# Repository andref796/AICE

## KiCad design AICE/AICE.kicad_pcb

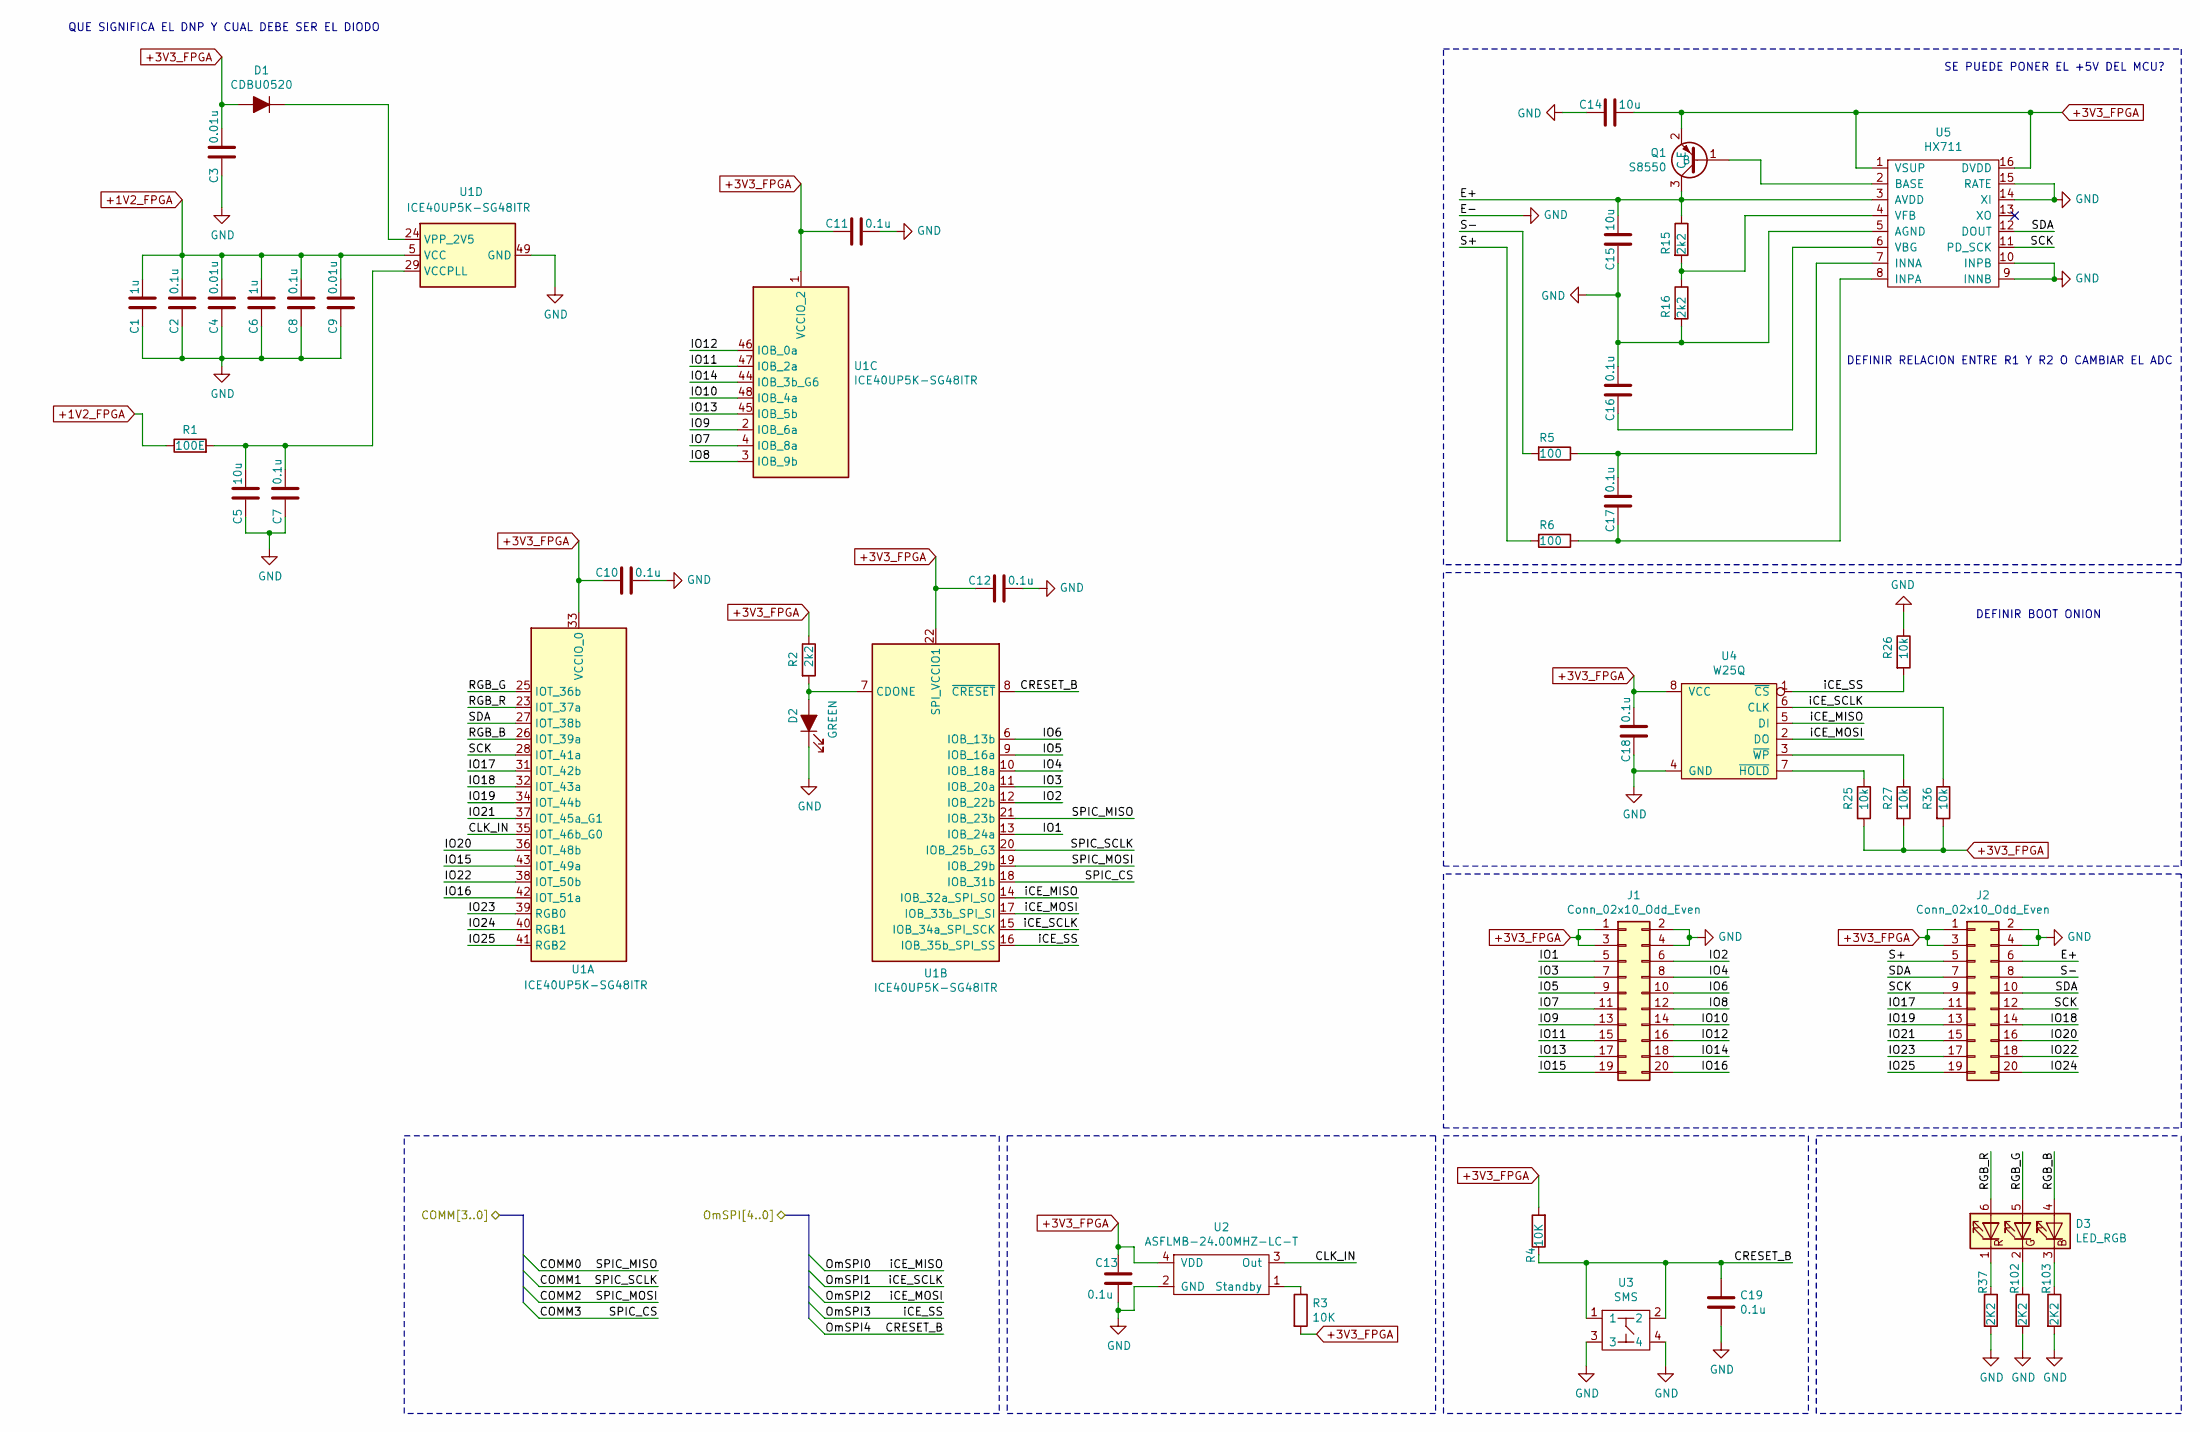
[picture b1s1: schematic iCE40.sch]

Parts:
C1, C6: 1u; C_0603_1608Metric
C2, C7, C8, C10, C11, C12, C13, C16, C17, C18, C19: 0.1u; C_0603_1608Metric
C3, C4, C9: 0.01u; C_0603_1608Metric
C5, C14, C15: 10u; C_0603_1608Metric
D1: CDBU0520; LED_0603_1608Metric
D2: GREEN; LED_0603_1608Metric
D3: LED_RGB; LED_RGB_Cree-PLCC-6_6x5mm_P2.1mm
J1, J2: Conn_02x10_Odd_Even; PinHeader_2x10_P2.54mm_Vertical
Q1: S8550; SOT-23
R1: 100E; R_0603_1608Metric
R2, R15, R16: 2k2; R_0603_1608Metric
R3, R4: 10K; R_0603_1608Metric
R5, R6: 100; R_0603_1608Metric
R25, R26, R27, R36: 10k; R_0603_1608Metric
R37, R102, R103: 2K2; R_0603_1608Metric
U1: ICE40UP5K-SG48ITR; QFN-48-1EP_7x7mm_P0.5mm_EP5.6x5.6mm
U2: ASFLMB-24.00MHZ-LC-T; ASFLMB
U3: SMS; SMS_BUTTON
U4: W25Q; SOIC-8_5.23x5.23mm_P1.27mm
U5: HX711; SOP-16_4.4x10.4mm_P1.27mm

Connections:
+1V2_FPGA: C1.1, C2.1, C4.1, C6.1, C8.1, C9.1, R1.1, U1.5 (VCC), U1.30 (VCC); also elsewhere on the board
+3V3_FPGA: C3.1, C10.2, C11.2, C12.2, C13.1, C14.1, C18.1, D1.2 (A), J1.1, J1.3, J2.1, J2.3, Q1.2 (E), R2.1, R3.2, R4.2, R25.2, R27.2, R36.2, U1.1 (VCCIO_2), U1.22 (SPI_VCCIO1), U1.33 (VCCIO_0), U2.4 (VDD), U4.8 (VCC), U5.1 (VSUP), U5.16 (DVDD); also elsewhere on the board
/iCE40/CLK_IN: U1.35 (IOT_46b_G0), U2.3 (Out)
/iCE40/COMM0: U1.21 (IOB_23b); also elsewhere on the board
/iCE40/COMM1: U1.20 (IOB_25b_G3); also elsewhere on the board
/iCE40/COMM2: U1.19 (IOB_29b); also elsewhere on the board
/iCE40/COMM3: U1.18 (IOB_31b); also elsewhere on the board
/iCE40/CRESET_B: C19.1, R4.1, U1.8 (~CRESET), U3.1, U3.2; also elsewhere on the board
/iCE40/E+: C15.1, J2.6, Q1.3 (C), R15.1, U5.3 (AVDD)
/iCE40/IO1: J1.5, U1.13 (IOB_24a)
/iCE40/IO2: J1.6, U1.12 (IOB_22b)
/iCE40/IO3: J1.7, U1.11 (IOB_20a)
/iCE40/IO4: J1.8, U1.10 (IOB_18a)
/iCE40/IO5: J1.9, U1.9 (IOB_16a)
/iCE40/IO6: J1.10, U1.6 (IOB_13b)
/iCE40/IO7: J1.11, U1.4 (IOB_8a)
/iCE40/IO8: J1.12, U1.3 (IOB_9b)
/iCE40/IO9: J1.13, U1.2 (IOB_6a)
/iCE40/IO10: J1.14, U1.48 (IOB_4a)
/iCE40/IO11: J1.15, U1.47 (IOB_2a)
/iCE40/IO12: J1.16, U1.46 (IOB_0a)
/iCE40/IO13: J1.17, U1.45 (IOB_5b)
/iCE40/IO14: J1.18, U1.44 (IOB_3b_G6)
/iCE40/IO15: J1.19, U1.43 (IOT_49a)
/iCE40/IO16: J1.20, U1.42 (IOT_51a)
/iCE40/IO17: J2.11, U1.31 (IOT_42b)
/iCE40/IO18: J2.14, U1.32 (IOT_43a)
/iCE40/IO19: J2.13, U1.34 (IOT_44b)
/iCE40/IO20: J2.16, U1.36 (IOT_48b)
/iCE40/IO21: J2.15, U1.37 (IOT_45a_G1)
/iCE40/IO22: J2.18, U1.38 (IOT_50b)
/iCE40/IO23: J2.17, U1.39 (RGB0)
/iCE40/IO24: J2.20, U1.40 (RGB1)
/iCE40/IO25: J2.19, U1.41 (RGB2)
/iCE40/OmSPI0: U1.14 (IOB_32a_SPI_SO), U4.5 (DI); also elsewhere on the board
/iCE40/OmSPI1: R36.1, U1.15 (IOB_34a_SPI_SCK), U4.6 (CLK); also elsewhere on the board
/iCE40/OmSPI2: U1.17 (IOB_33b_SPI_SI), U4.2 (DO); also elsewhere on the board
/iCE40/OmSPI3: R26.2, U1.16 (IOB_35b_SPI_SS), U4.1 (~CS~); also elsewhere on the board
/iCE40/RGB_B: D3.4 (BA), U1.26 (IOT_39a)
/iCE40/RGB_G: D3.5 (GA), U1.25 (IOT_36b)
/iCE40/RGB_R: D3.6 (RA), U1.23 (IOT_37a)
/iCE40/S+: J2.5, R6.2
/iCE40/S-: J2.8, R5.2
GND: C1.2, C2.2, C3.2, C4.2, C5.2, C6.2, C7.2, C8.2, C9.2, C10.1, C11.1, C12.1, C13.2, C14.2, C15.2, C16.1, C18.2, C19.2, D2.1 (K), J1.2, J1.4, J2.2, J2.4, R16.2, R26.1, R37.2, R102.2, R103.2, U1.49 (GND), U2.2 (GND), U3.3, U3.4, U4.4 (GND), U5.5 (AGND), U5.9 (INNB), U5.10 (INPB), U5.14 (XI), U5.15 (RATE); also elsewhere on the board
unnamed: C5.1, C7.1, R1.2, U1.29 (VCCPLL)
unnamed: C16.2, U5.6 (VBG)
unnamed: C17.1, R5.1, U5.7 (INNA)
unnamed: C17.2, R6.1, U5.8 (INPA)
unnamed: D1.1 (K), U1.24 (VPP_2V5)
unnamed: D2.2 (A), R2.2, U1.7 (CDONE)
unnamed: D3.1 (RK), R37.1
unnamed: D3.2 (GK), R102.1
unnamed: D3.3 (BK), R103.1
unnamed: Q1.1 (B), U5.2 (BASE)
unnamed: R3.1, U2.1 (Standby)
unnamed: R15.2, R16.1, U5.4 (VFB)
unnamed: R25.1, U4.7 (~HOLD)
unnamed: R27.1, U4.3 (~WP)

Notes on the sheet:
SE PUEDE PONER EL +5V DEL MCU?
QUE SIGNIFICA EL DNP Y CUAL DEBE SER EL DIODO
DEFINIR BOOT ONION
DEFINIR RELACION ENTRE R1 Y R2 O CAMBIAR EL ADC

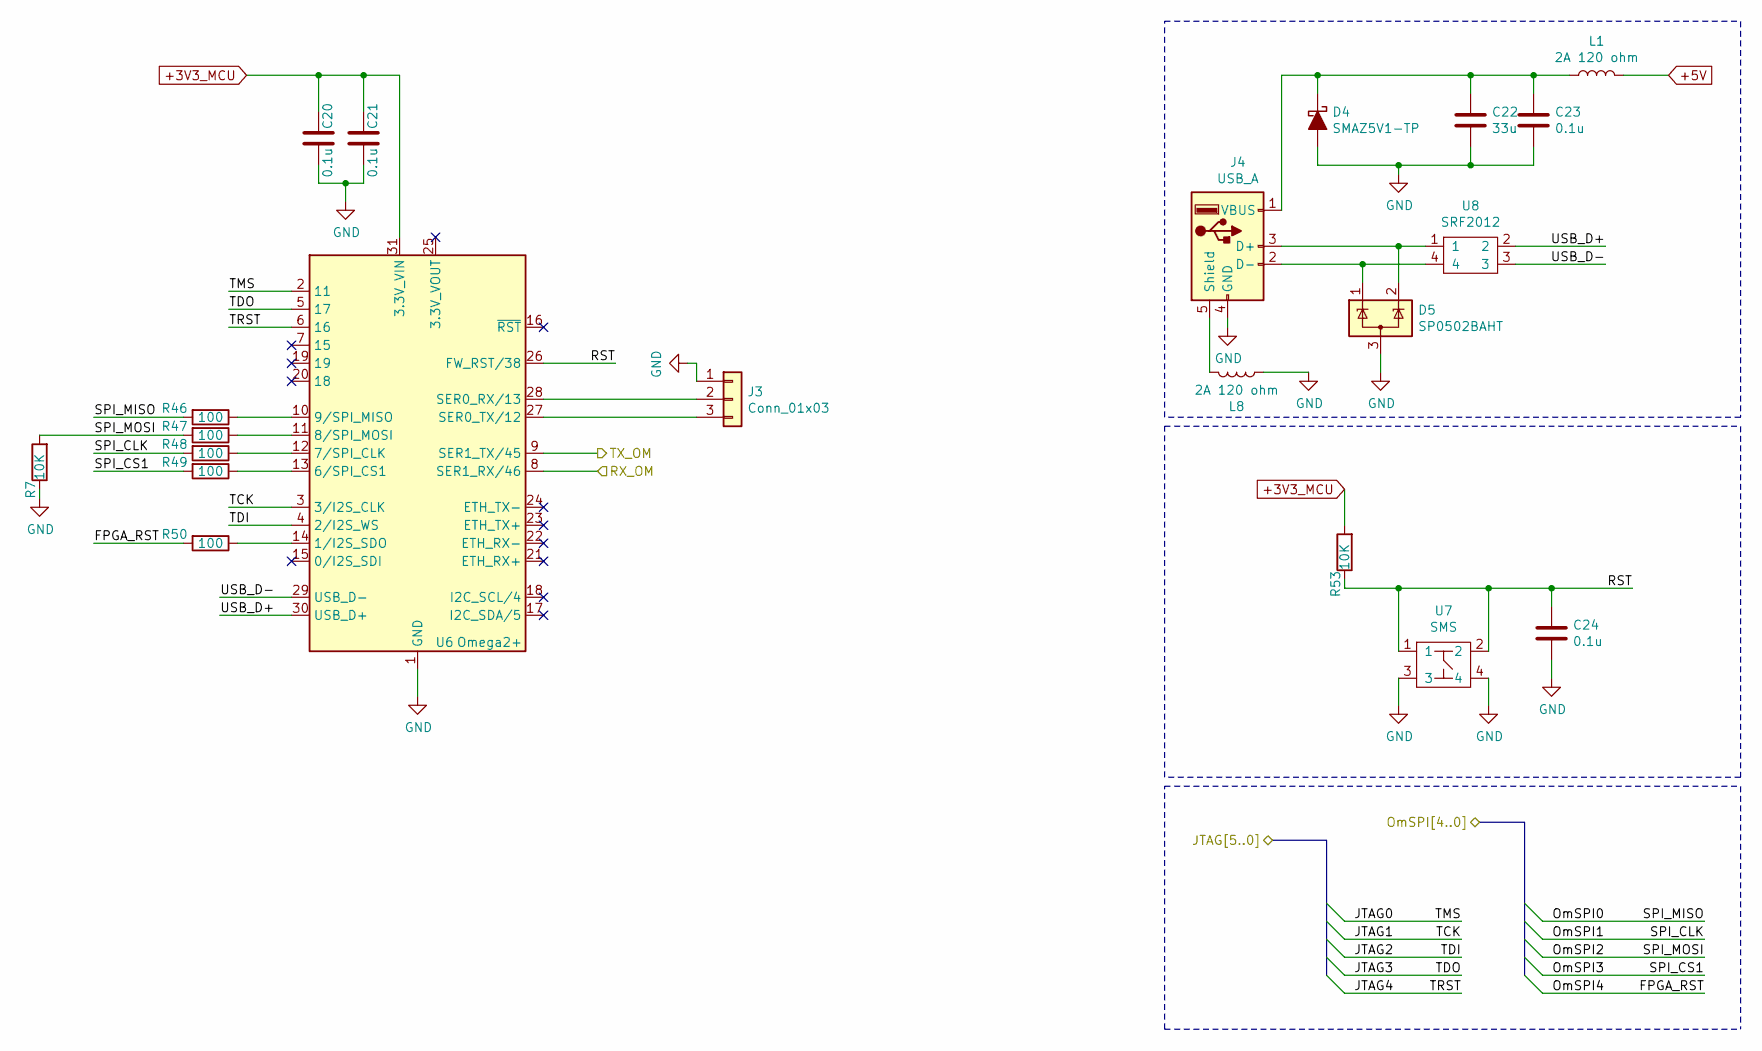
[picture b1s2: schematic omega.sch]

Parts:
C20, C21, C23, C24: 0.1u; C_0603_1608Metric
C22: 33u; CP_Radial_D5.0mm_P2.00mm
D4: SMAZ5V1-TP; D_SMA
D5: SP0502BAHT; SOT-23
J3: Conn_01x03; PinHeader_1x03_P2.54mm_Vertical
J4: USB_A; USB_A_Stewart_SS-52100-001_Horizontal
L1, L8: 2A 120 ohm; L_0805_2012Metric
R7, R53: 10K; R_0603_1608Metric
R46, R47, R48, R49, R50: 100; R_0603_1608Metric
U6: Omega2+; Onion_Omega2+
U7: SMS; SMS_BUTTON
U8: SRF2012

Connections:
+3V3_MCU: C20.2, C21.2, R53.2, U6.31 (3.3V_VIN); also elsewhere on the board
+5V: L1.2; also elsewhere on the board
/iCE40/CRESET_B: R50.2; also elsewhere on the board
/iCE40/OmSPI0: R46.2; also elsewhere on the board
/iCE40/OmSPI1: R48.2; also elsewhere on the board
/iCE40/OmSPI2: R7.2, R47.2; also elsewhere on the board
/iCE40/OmSPI3: R49.2; also elsewhere on the board
/omega/JTAG0: U6.2 (11); also elsewhere on the board
/omega/JTAG1: U6.3 (3/I2S_CLK); also elsewhere on the board
/omega/JTAG2: U6.4 (2/I2S_WS); also elsewhere on the board
/omega/JTAG3: U6.5 (17); also elsewhere on the board
/omega/JTAG4: U6.6 (16); also elsewhere on the board
/omega/RST: C24.1, R53.1, U6.26 (FW_RST/38), U7.1, U7.2
/omega/RX_OM: U6.8 (SER1_RX/46); also elsewhere on the board
/omega/USB_D+: U6.30 (USB_D+), U8.2
/omega/USB_D-: U6.29 (USB_D-), U8.3
/sipeedm1w/RX_M1: U6.9 (SER1_TX/45); also elsewhere on the board
GND: C20.1, C21.1, C22.2, C23.2, C24.2, D4.2 (A), D5.3 (A), J3.1, J4.4 (GND), L8.1, R7.1, U6.1 (GND), U6.32 (GND), U7.3, U7.4; also elsewhere on the board
unnamed: C22.1, C23.1, D4.1 (K), J4.1 (VBUS), L1.1
unnamed: D5.1 (K), J4.2 (D-), U8.4
unnamed: D5.2 (K), J4.3 (D+), U8.1
unnamed: J3.2, U6.28 (SER0_RX/13)
unnamed: J3.3, U6.27 (SER0_TX/12)
unnamed: J4.5 (Shield), L8.2
unnamed: R46.1, U6.10 (9/SPI_MISO)
unnamed: R47.1, U6.11 (8/SPI_MOSI)
unnamed: R48.1, U6.12 (7/SPI_CLK)
unnamed: R49.1, U6.13 (6/SPI_CS1)
unnamed: R50.1, U6.14 (1/I2S_SDO)

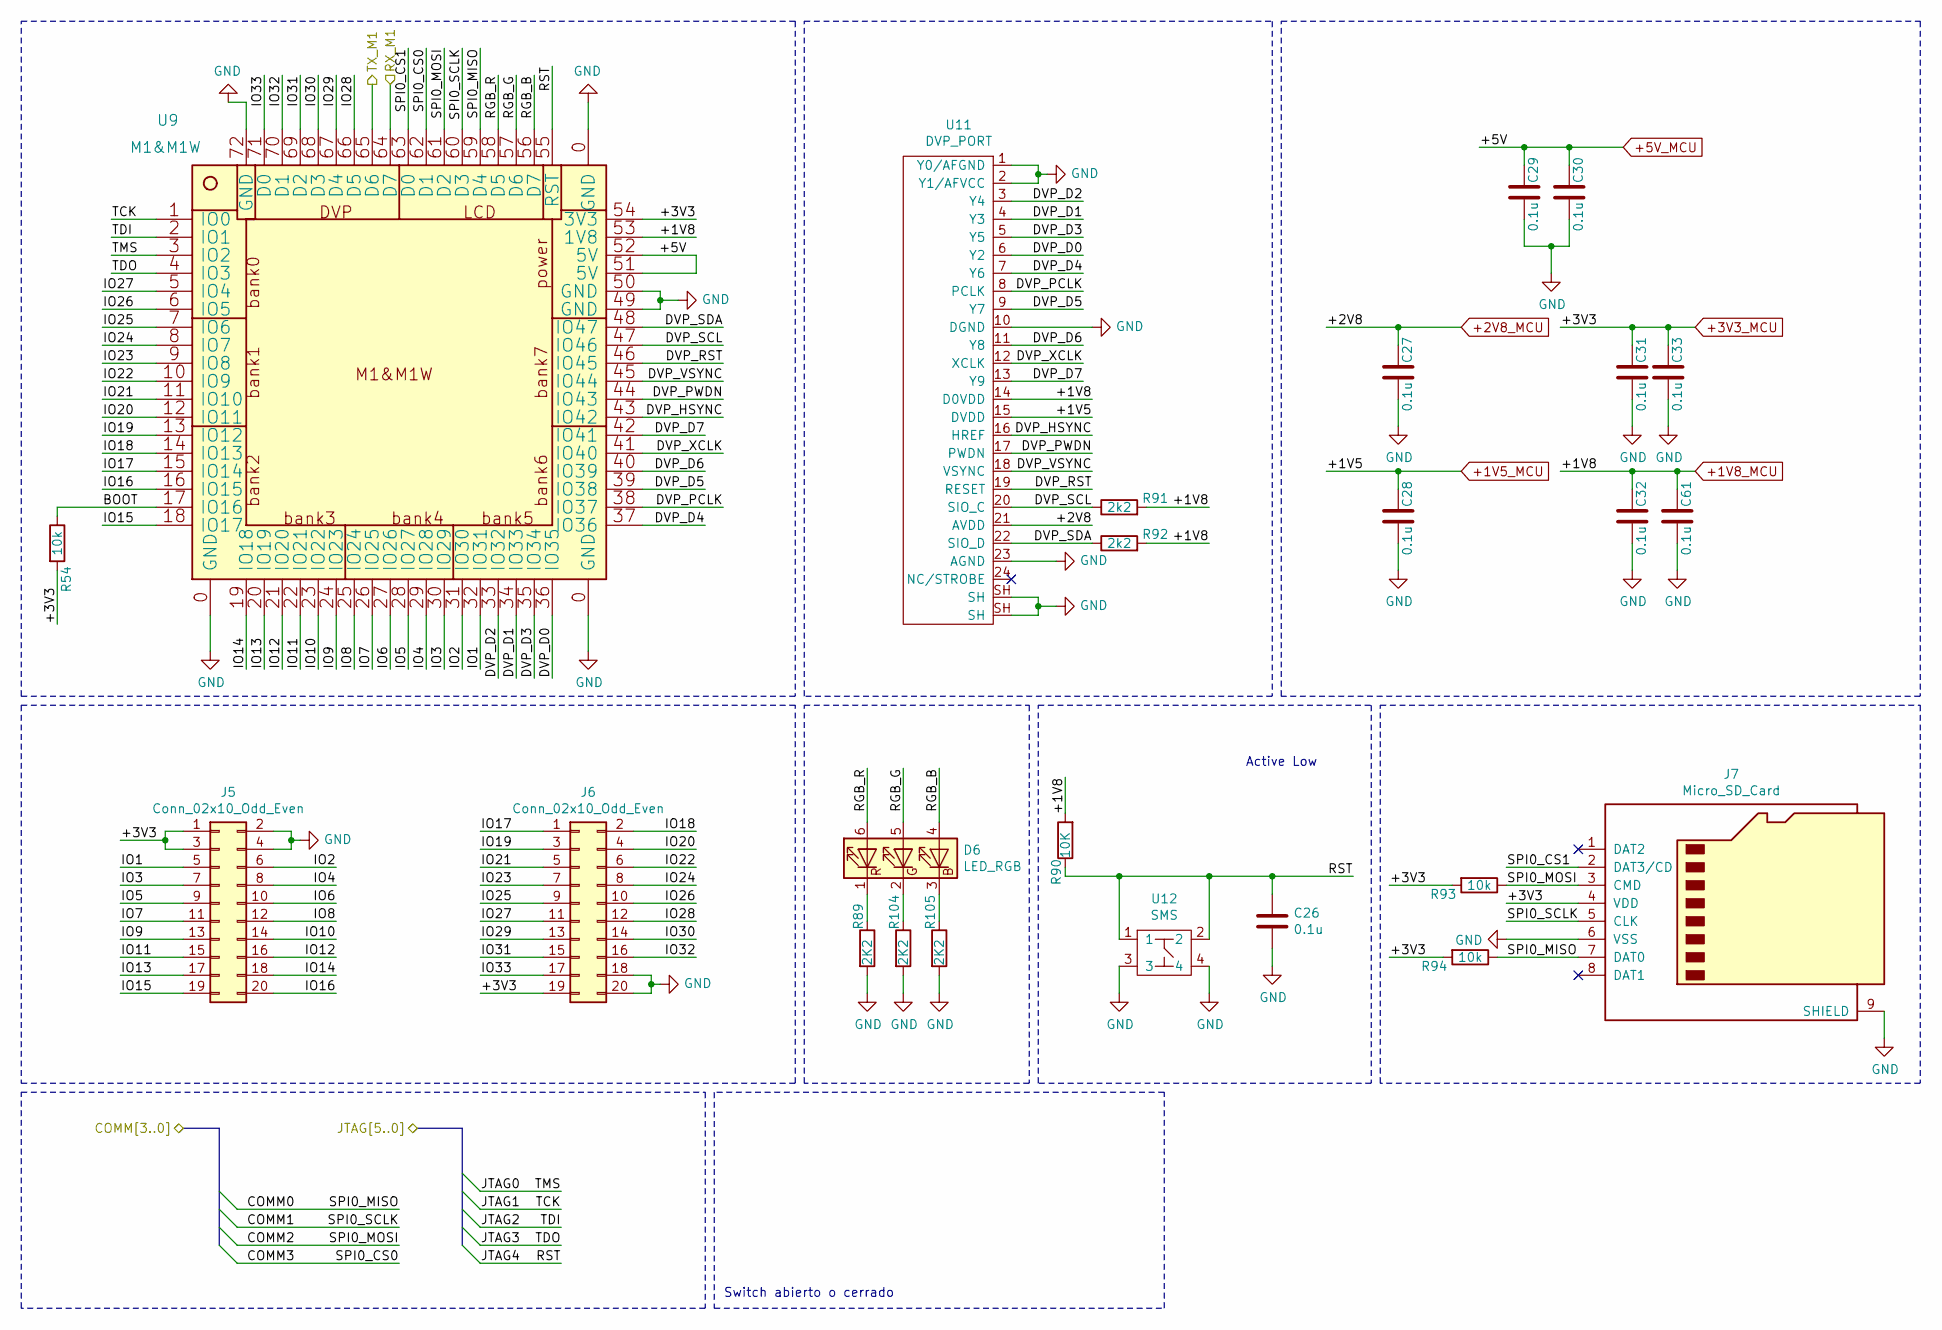
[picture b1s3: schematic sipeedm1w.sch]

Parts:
C26, C27, C28, C29, C30, C31, C32, C33, C61: 0.1u; C_0603_1608Metric
D6: LED_RGB; LED_RGB_Cree-PLCC-6_6x5mm_P2.1mm
J5, J6: Conn_02x10_Odd_Even; PinHeader_2x10_P2.54mm_Vertical
J7: Micro_SD_Card; microSD_HC_Wuerth_693072010801
R54, R93, R94: 10k; R_0603_1608Metric
R89, R104, R105: 2K2; R_0603_1608Metric
R90: 10K; R_0603_1608Metric
R91, R92: 2k2; R_0603_1608Metric
U9: M1&M1W; QFN-72_25.4x25.4_Pitch1.27mm
U11: DVP_PORT; Molex_502231-2400_1x24-1SH_P0.5mm_Vertical
U12: SMS; SMS_BUTTON

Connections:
+1V5_MCU: C28.2, U11.15 (DVDD); also elsewhere on the board
+1V8_MCU: C32.2, C61.2, R90.2, R91.2, R92.2, U9.53 (1V8), U11.14 (D0VDD); also elsewhere on the board
+2V8_MCU: C27.2, U11.21 (AVDD); also elsewhere on the board
+3V3_MCU: C31.2, C33.2, J5.1, J5.3, J6.19, J7.4 (VDD), R54.2, R93.2, R94.2, U9.54 (3V3); also elsewhere on the board
+5V: C29.2, C30.2, U9.51 (5V), U9.52 (5V); also elsewhere on the board
/iCE40/COMM0: J7.7 (DAT0), R94.1, U9.59 (D4); also elsewhere on the board
/iCE40/COMM1: J7.5 (CLK), U9.60 (D3); also elsewhere on the board
/iCE40/COMM2: J7.3 (CMD), R93.1, U9.61 (D2); also elsewhere on the board
/iCE40/COMM3: U9.62 (D1); also elsewhere on the board
/omega/JTAG0: U9.3 (IO2); also elsewhere on the board
/omega/JTAG1: U9.1 (IO0); also elsewhere on the board
/omega/JTAG2: U9.2 (IO1); also elsewhere on the board
/omega/JTAG3: U9.4 (IO3); also elsewhere on the board
/omega/JTAG4: C26.1, R90.1, U9.55 (RST), U12.1, U12.2; also elsewhere on the board
/omega/RX_OM: U9.65 (D6); also elsewhere on the board
/sipeedm1w/BOOT: R54.1, U9.17 (IO16)
/sipeedm1w/DVP_D0: U9.36 (IO35), U11.6 (Y2)
/sipeedm1w/DVP_D1: U9.34 (IO33), U11.4 (Y3)
/sipeedm1w/DVP_D2: U9.33 (IO32), U11.3 (Y4)
/sipeedm1w/DVP_D3: U9.35 (IO34), U11.5 (Y5)
/sipeedm1w/DVP_D4: U9.37 (IO36), U11.7 (Y6)
/sipeedm1w/DVP_D5: U9.39 (IO38), U11.9 (Y7)
/sipeedm1w/DVP_D6: U9.40 (IO39), U11.11 (Y8)
/sipeedm1w/DVP_D7: U9.42 (IO41), U11.13 (Y9)
/sipeedm1w/DVP_HSYNC: U9.43 (IO42), U11.16 (HREF)
/sipeedm1w/DVP_PCLK: U9.38 (IO37), U11.8 (PCLK)
/sipeedm1w/DVP_PWDN: U9.44 (IO43), U11.17 (PWDN)
/sipeedm1w/DVP_RST: U9.46 (IO45), U11.19 (RESET)
/sipeedm1w/DVP_SCL: R91.1, U9.47 (IO46), U11.20 (SIO_C)
/sipeedm1w/DVP_SDA: R92.1, U9.48 (IO47), U11.22 (SIO_D)
/sipeedm1w/DVP_VSYNC: U9.45 (IO44), U11.18 (VSYNC)
/sipeedm1w/DVP_XCLK: U9.41 (IO40), U11.12 (XCLK)
/sipeedm1w/IO1: J5.5, U9.32 (IO31)
/sipeedm1w/IO2: J5.6, U9.31 (IO30)
/sipeedm1w/IO3: J5.7, U9.30 (IO29)
/sipeedm1w/IO4: J5.8, U9.29 (IO28)
/sipeedm1w/IO5: J5.9, U9.28 (IO27)
/sipeedm1w/IO6: J5.10, U9.27 (IO26)
/sipeedm1w/IO7: J5.11, U9.26 (IO25)
/sipeedm1w/IO8: J5.12, U9.25 (IO24)
/sipeedm1w/IO9: J5.13, U9.24 (IO23)
/sipeedm1w/IO10: J5.14, U9.23 (IO22)
/sipeedm1w/IO11: J5.15, U9.22 (IO21)
/sipeedm1w/IO12: J5.16, U9.21 (IO20)
/sipeedm1w/IO13: J5.17, U9.20 (IO19)
/sipeedm1w/IO14: J5.18, U9.19 (IO18)
/sipeedm1w/IO15: J5.19, U9.18 (IO17)
/sipeedm1w/IO16: J5.20, U9.16 (IO15)
/sipeedm1w/IO17: J6.1, U9.15 (IO14)
/sipeedm1w/IO18: J6.2, U9.14 (IO13)
/sipeedm1w/IO19: J6.3, U9.13 (IO12)
/sipeedm1w/IO20: J6.4, U9.12 (IO11)
/sipeedm1w/IO21: J6.5, U9.11 (IO10)
/sipeedm1w/IO22: J6.6, U9.10 (IO9)
/sipeedm1w/IO23: J6.7, U9.9 (IO8)
/sipeedm1w/IO24: J6.8, U9.8 (IO7)
/sipeedm1w/IO25: J6.9, U9.7 (IO6)
/sipeedm1w/IO26: J6.10, U9.6 (IO5)
/sipeedm1w/IO27: J6.11, U9.5 (IO4)
/sipeedm1w/IO28: J6.12, U9.66 (D5)
/sipeedm1w/IO29: J6.13, U9.67 (D4)
/sipeedm1w/IO30: J6.14, U9.68 (D3)
/sipeedm1w/IO31: J6.15, U9.69 (D2)
/sipeedm1w/IO32: J6.16, U9.70 (D1)
/sipeedm1w/IO33: J6.17, U9.71 (D0)
/sipeedm1w/RGB_B: D6.4 (BA), U9.56 (D7)
/sipeedm1w/RGB_G: D6.5 (GA), U9.57 (D6)
/sipeedm1w/RGB_R: D6.6 (RA), U9.58 (D5)
/sipeedm1w/RX_M1: U9.64 (D7); also elsewhere on the board
/sipeedm1w/SPI0_CS1: J7.2 (DAT3/CD), U9.63 (D0)
GND: C26.2, C27.1, C28.1, C29.1, C30.1, C31.1, C32.1, C33.1, C61.1, J5.2, J5.4, J6.18, J6.20, J7.6 (VSS), J7.9 (SHIELD), R89.2, R104.2, R105.2, U9.0 (GND), U9.49 (GND), U9.50 (GND), U9.72 (GND), U11.1 (Y0/AFGND), U11.2 (Y1/AFVCC), U11.10 (DGND), U11.23 (AGND), U11.SH, U12.3, U12.4; also elsewhere on the board
unnamed: D6.1 (RK), R89.1
unnamed: D6.2 (GK), R104.1
unnamed: D6.3 (BK), R105.1

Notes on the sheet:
Switch abierto o cerrado
Active Low

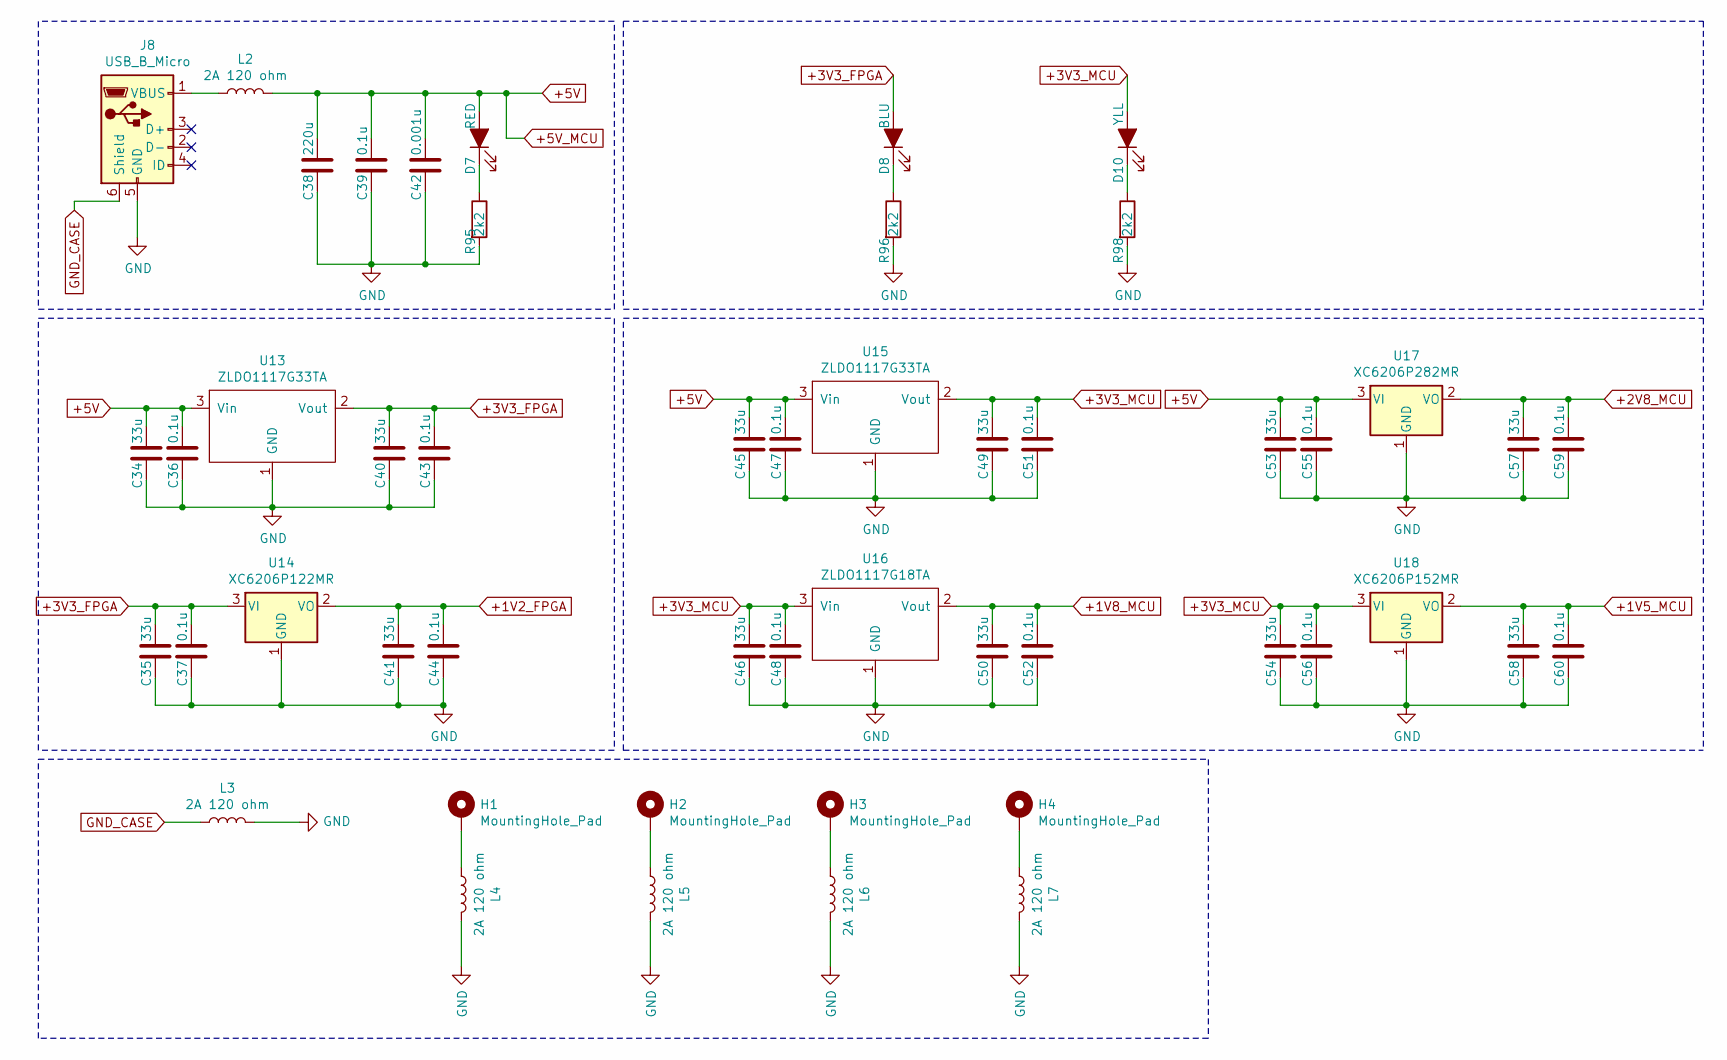
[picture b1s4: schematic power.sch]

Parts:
C34, C35, C40, C41, C45, C46, C49, C50, C53, C54, C57, C58: 33u; C_0805_2012Metric
C36, C37, C39, C43, C44, C47, C48, C51, C52, C55, C56, C59, C60: 0.1u; C_0603_1608Metric
C38: 220u; C_1206_3216Metric
C42: 0.001u; C_0603_1608Metric
D7: RED; LED_0603_1608Metric
D8: BLU; LED_0603_1608Metric
D10: YLL; LED_0603_1608Metric
H1, H2, H3, H4: MountingHole_Pad; MountingHole_2.5mm_Pad
J8: USB_B_Micro; USB_Micro-B_Molex_47346-0001
L2, L3, L4, L5, L6, L7: 2A 120 ohm; L_0805_2012Metric
R95, R96, R98: 2k2; R_0603_1608Metric
U13, U15: ZLDO1117G33TA; SOT-223
U14: XC6206P122MR; SOT-23
U16: ZLDO1117G18TA; SOT-223
U17: XC6206P282MR; SOT-23
U18: XC6206P152MR; SOT-23

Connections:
+1V2_FPGA: C41.1, C44.1, U14.2 (VO); also elsewhere on the board
+1V5_MCU: C58.1, C60.1, U18.2 (VO); also elsewhere on the board
+1V8_MCU: C50.1, C52.1, U16.2 (Vout); also elsewhere on the board
+2V8_MCU: C57.1, C59.1, U17.2 (VO); also elsewhere on the board
+3V3_FPGA: C35.1, C37.1, C40.1, C43.1, D8.2 (A), U13.2 (Vout), U14.3 (VI); also elsewhere on the board
+3V3_MCU: C46.1, C48.1, C49.1, C51.1, C54.1, C56.1, D10.2 (A), U15.2 (Vout), U16.3 (Vin), U18.3 (VI); also elsewhere on the board
+5V: C34.1, C36.1, C38.1, C39.1, C42.1, C45.1, C47.1, C53.1, C55.1, D7.2 (A), L2.2, U13.3 (Vin), U15.3 (Vin), U17.3 (VI); also elsewhere on the board
GND: C34.2, C35.2, C36.2, C37.2, C38.2, C39.2, C40.2, C41.2, C42.2, C43.2, C44.2, C45.2, C46.2, C47.2, C48.2, C49.2, C50.2, C51.2, C52.2, C53.2, C54.2, C55.2, C56.2, C57.2, C58.2, C59.2, C60.2, J8.5 (GND), L3.2, L4.2, L5.2, L6.2, L7.2, R95.2, R96.2, R98.2, U13.1 (GND), U14.1 (GND), U15.1 (GND), U16.1 (GND), U17.1 (GND), U18.1 (GND); also elsewhere on the board
GND_CASE: J8.6 (Shield), L3.1
unnamed: D7.1 (K), R95.1
unnamed: D8.1 (K), R96.1
unnamed: D10.1 (K), R98.1
unnamed: H1.1, L4.1
unnamed: H2.1, L5.1
unnamed: H3.1, L6.1
unnamed: H4.1, L7.1
unnamed: J8.1 (VBUS), L2.1

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
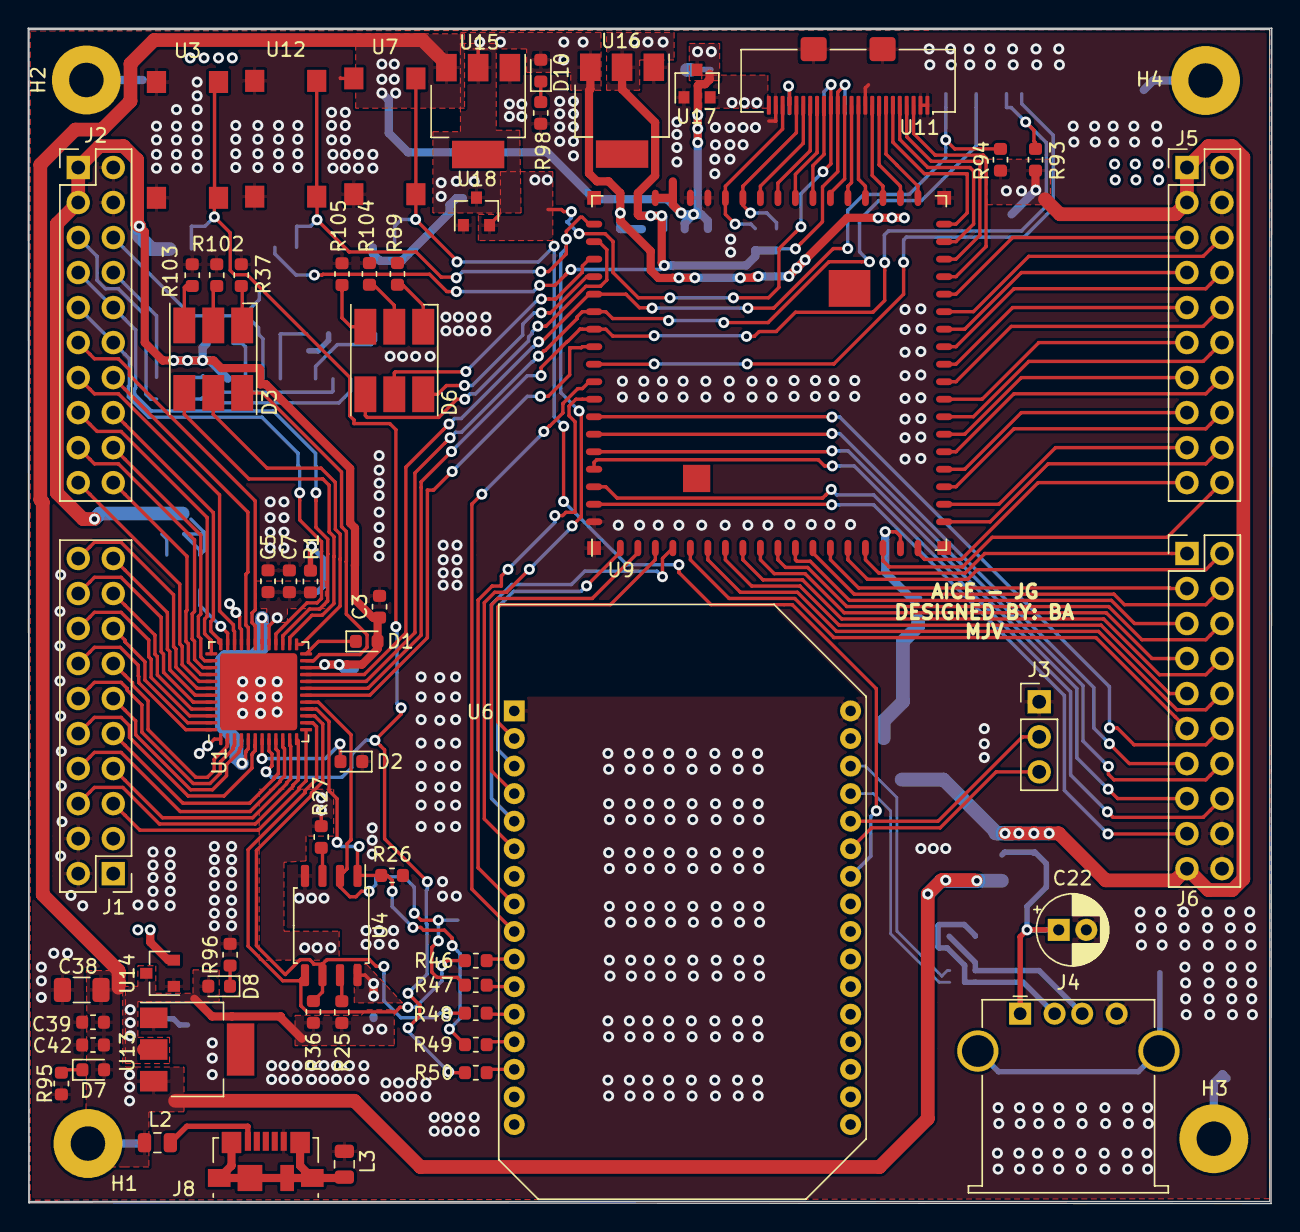
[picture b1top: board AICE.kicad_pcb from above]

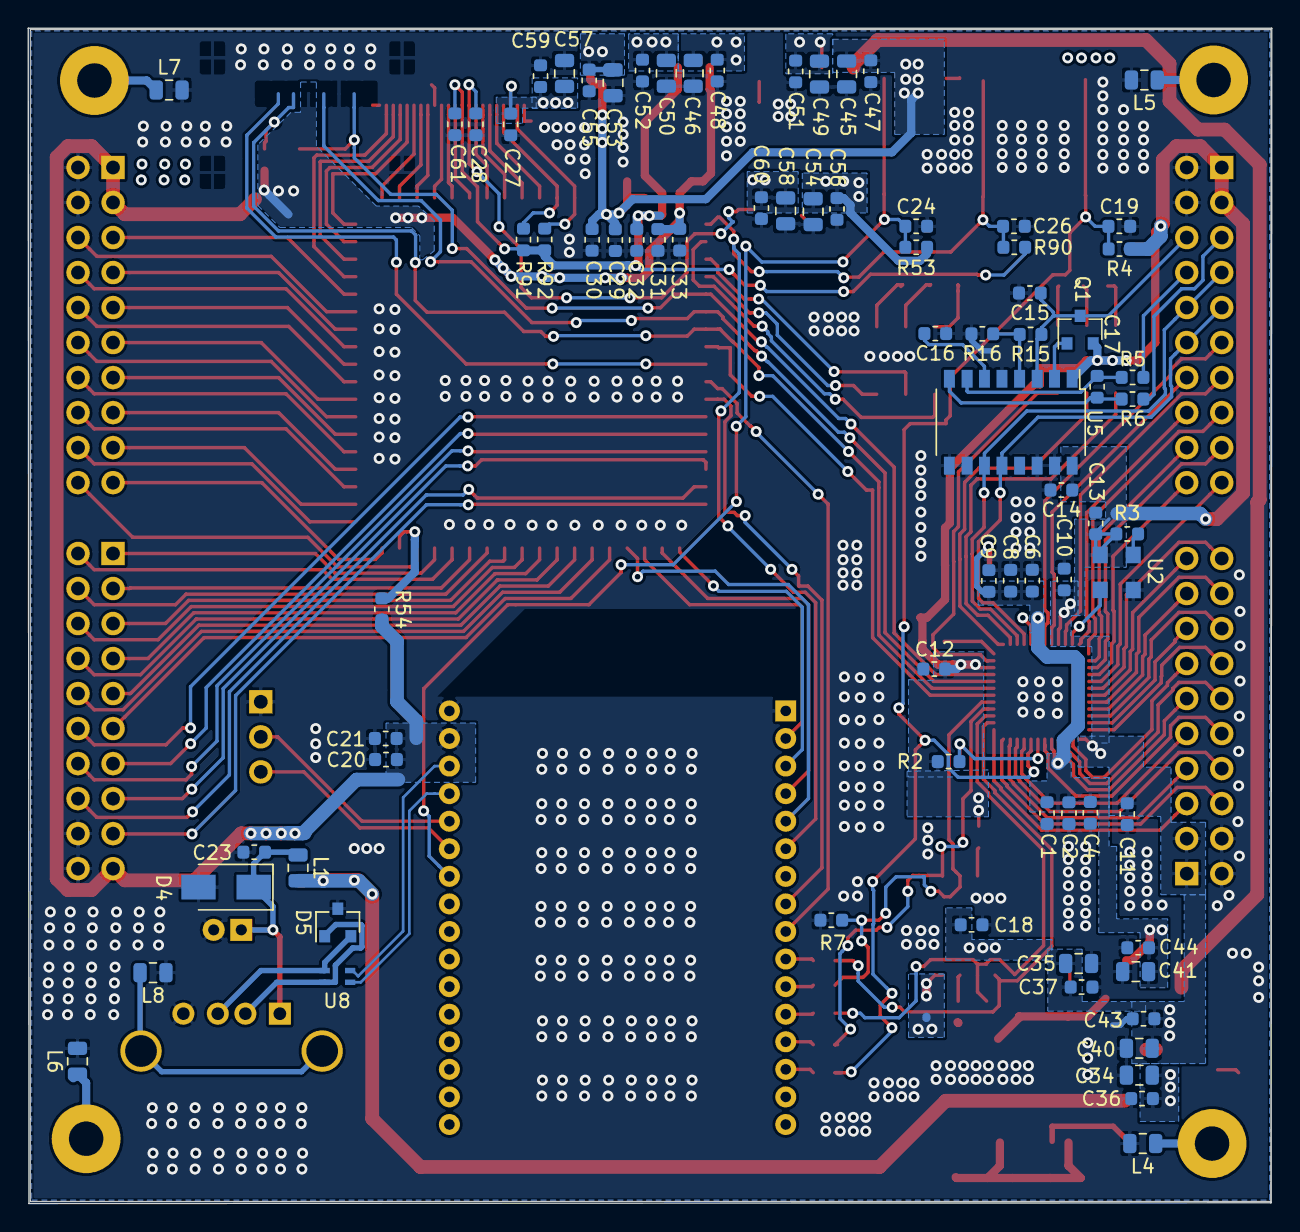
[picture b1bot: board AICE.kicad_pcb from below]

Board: 2 copper layers, 90.2 x 85.2 mm, 140 parts (78 on the bottom side), 151 nets.
